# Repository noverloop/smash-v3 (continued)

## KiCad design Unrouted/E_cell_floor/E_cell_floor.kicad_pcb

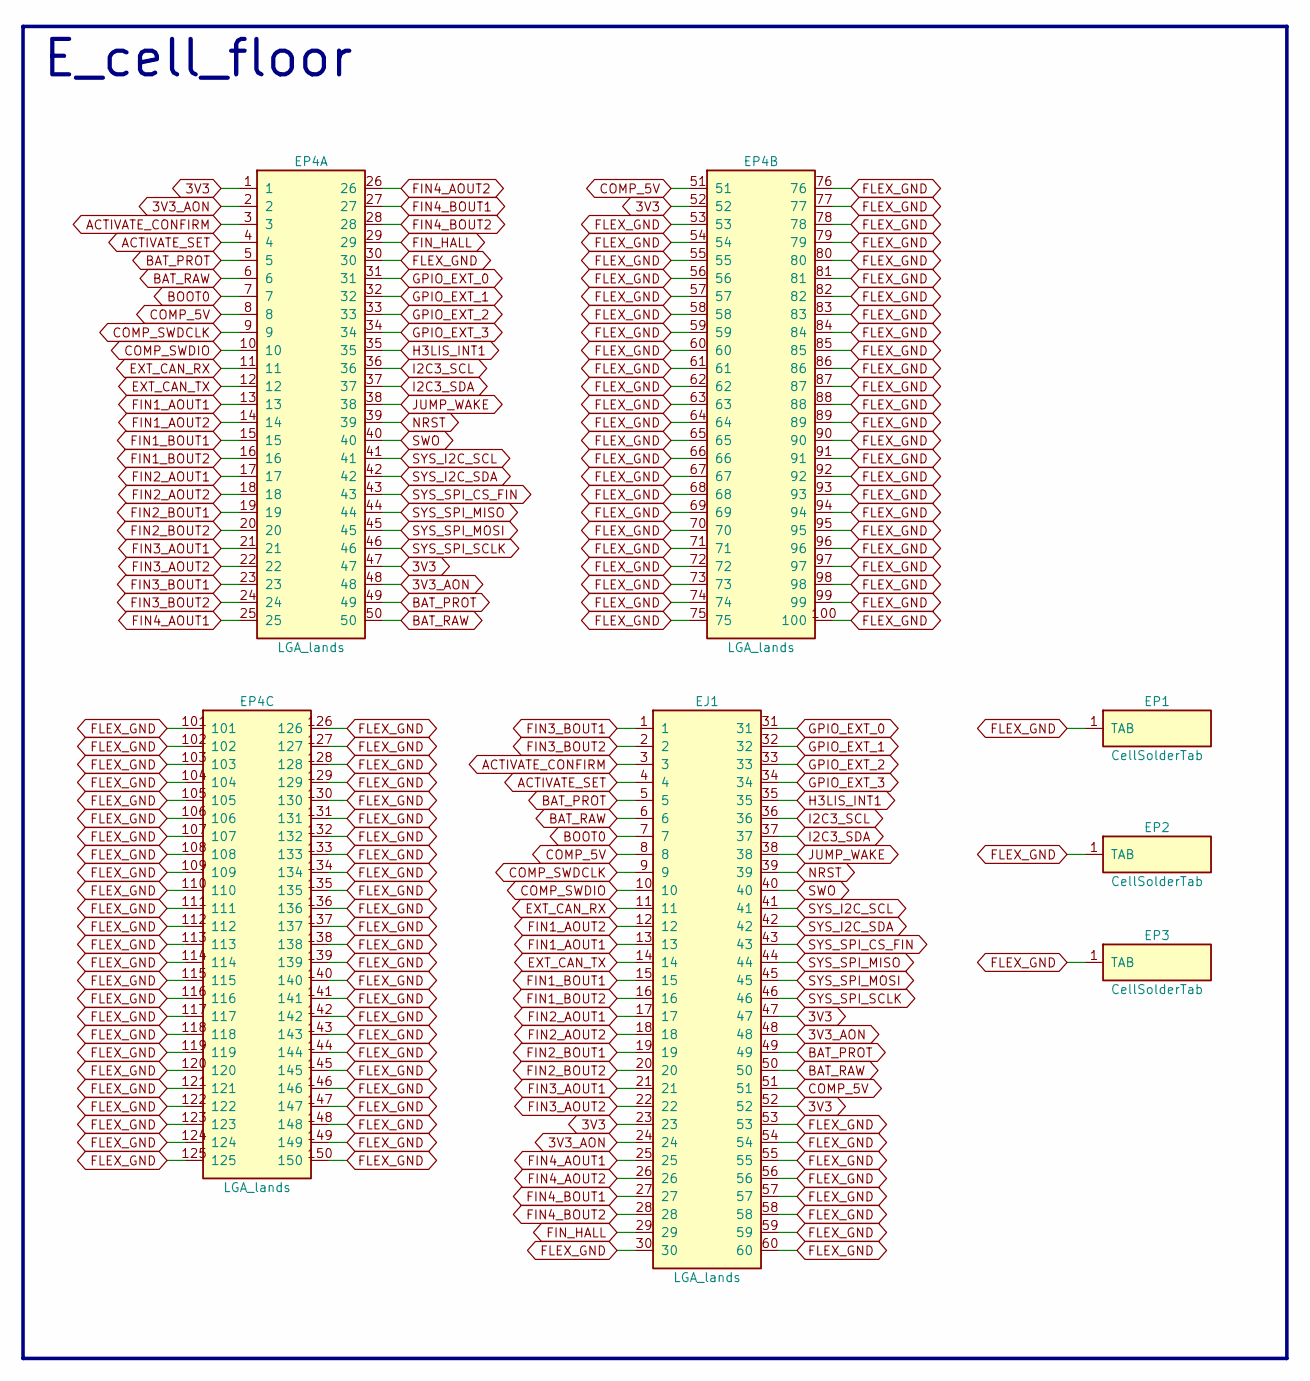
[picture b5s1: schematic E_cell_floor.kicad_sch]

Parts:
EJ1: LGA_lands; J_cell_floor_board_spacer_battery_1; MPN LGA_lands
EP1, EP2, EP3: CellSolderTab; CellSolderTab_placeholder; MPN CellSolderTab
EP4: LGA_lands; P_cell_floor_board_spacer_activation_interface_cell_floor_b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; MPN LGA_lands

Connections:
3V3: EJ1.23, EJ1.47, EJ1.52, EP4.1, EP4.47, EP4.52
3V3_AON: EJ1.24, EJ1.48, EP4.2, EP4.48
ACTIVATE_CONFIRM: EJ1.3, EP4.3
ACTIVATE_SET: EJ1.4, EP4.4
BAT_PROT: EJ1.5, EJ1.49, EP4.5, EP4.49
BAT_RAW: EJ1.6, EJ1.50, EP4.6, EP4.50
BOOT0: EJ1.7, EP4.7
COMP_5V: EJ1.8, EJ1.51, EP4.8, EP4.51
COMP_SWDCLK: EJ1.9, EP4.9
COMP_SWDIO: EJ1.10, EP4.10
EXT_CAN_RX: EJ1.11, EP4.11
EXT_CAN_TX: EJ1.14, EP4.12
FIN1_AOUT1: EJ1.13, EP4.13
FIN1_AOUT2: EJ1.12, EP4.14
FIN1_BOUT1: EJ1.15, EP4.15
FIN1_BOUT2: EJ1.16, EP4.16
FIN2_AOUT1: EJ1.17, EP4.17
FIN2_AOUT2: EJ1.18, EP4.18
FIN2_BOUT1: EJ1.19, EP4.19
FIN2_BOUT2: EJ1.20, EP4.20
FIN3_AOUT1: EJ1.21, EP4.21
FIN3_AOUT2: EJ1.22, EP4.22
FIN3_BOUT1: EJ1.1, EP4.23
FIN3_BOUT2: EJ1.2, EP4.24
FIN4_AOUT1: EJ1.25, EP4.25
FIN4_AOUT2: EJ1.26, EP4.26
FIN4_BOUT1: EJ1.27, EP4.27
FIN4_BOUT2: EJ1.28, EP4.28
FIN_HALL: EJ1.29, EP4.29
FLEX_GND: EJ1.30, EJ1.53, EJ1.54, EJ1.55, EJ1.56, EJ1.57, EJ1.58, EJ1.59, EJ1.60, EP1.1, EP2.1, EP3.1, EP4.30, EP4.53, EP4.54, EP4.55, EP4.56, EP4.57, EP4.58, EP4.59, EP4.60, EP4.61, EP4.62, EP4.63, EP4.64, EP4.65, EP4.66, EP4.67, EP4.68, EP4.69, EP4.70, EP4.71, EP4.72, EP4.73, EP4.74, EP4.75, EP4.76, EP4.77, EP4.78, EP4.79, EP4.80, EP4.81, EP4.82, EP4.83, EP4.84, EP4.85, EP4.86, EP4.87, EP4.88, EP4.89, EP4.90, EP4.91, EP4.92, EP4.93, EP4.94, EP4.95, EP4.96, EP4.97, EP4.98, EP4.99, EP4.100, EP4.101, EP4.102, EP4.103, EP4.104, EP4.105, EP4.106, EP4.107, EP4.108, EP4.109, EP4.110, EP4.111, EP4.112, EP4.113, EP4.114, EP4.115, EP4.116, EP4.117, EP4.118, EP4.119, EP4.120, EP4.121, EP4.122, EP4.123, EP4.124, EP4.125, EP4.126, EP4.127, EP4.128, EP4.129, EP4.130, EP4.131, EP4.132, EP4.133, EP4.134, EP4.135, EP4.136, EP4.137, EP4.138, EP4.139, EP4.140, EP4.141, EP4.142, EP4.143, EP4.144, EP4.145, EP4.146, EP4.147, EP4.148, EP4.149, EP4.150
GPIO_EXT_0: EJ1.31, EP4.31
GPIO_EXT_1: EJ1.32, EP4.32
GPIO_EXT_2: EJ1.33, EP4.33
GPIO_EXT_3: EJ1.34, EP4.34
H3LIS_INT1: EJ1.35, EP4.35
I2C3_SCL: EJ1.36, EP4.36
I2C3_SDA: EJ1.37, EP4.37
JUMP_WAKE: EJ1.38, EP4.38
NRST: EJ1.39, EP4.39
SWO: EJ1.40, EP4.40
SYS_I2C_SCL: EJ1.41, EP4.41
SYS_I2C_SDA: EJ1.42, EP4.42
SYS_SPI_CS_FIN: EJ1.43, EP4.43
SYS_SPI_MISO: EJ1.44, EP4.44
SYS_SPI_MOSI: EJ1.45, EP4.45
SYS_SPI_SCLK: EJ1.46, EP4.46

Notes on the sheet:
E_cell_floor

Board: 6 copper layers, 7 parts (1 on the bottom side), 46 nets, no tracks yet.

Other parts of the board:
EMH1, EMH2: smash_mech_potting

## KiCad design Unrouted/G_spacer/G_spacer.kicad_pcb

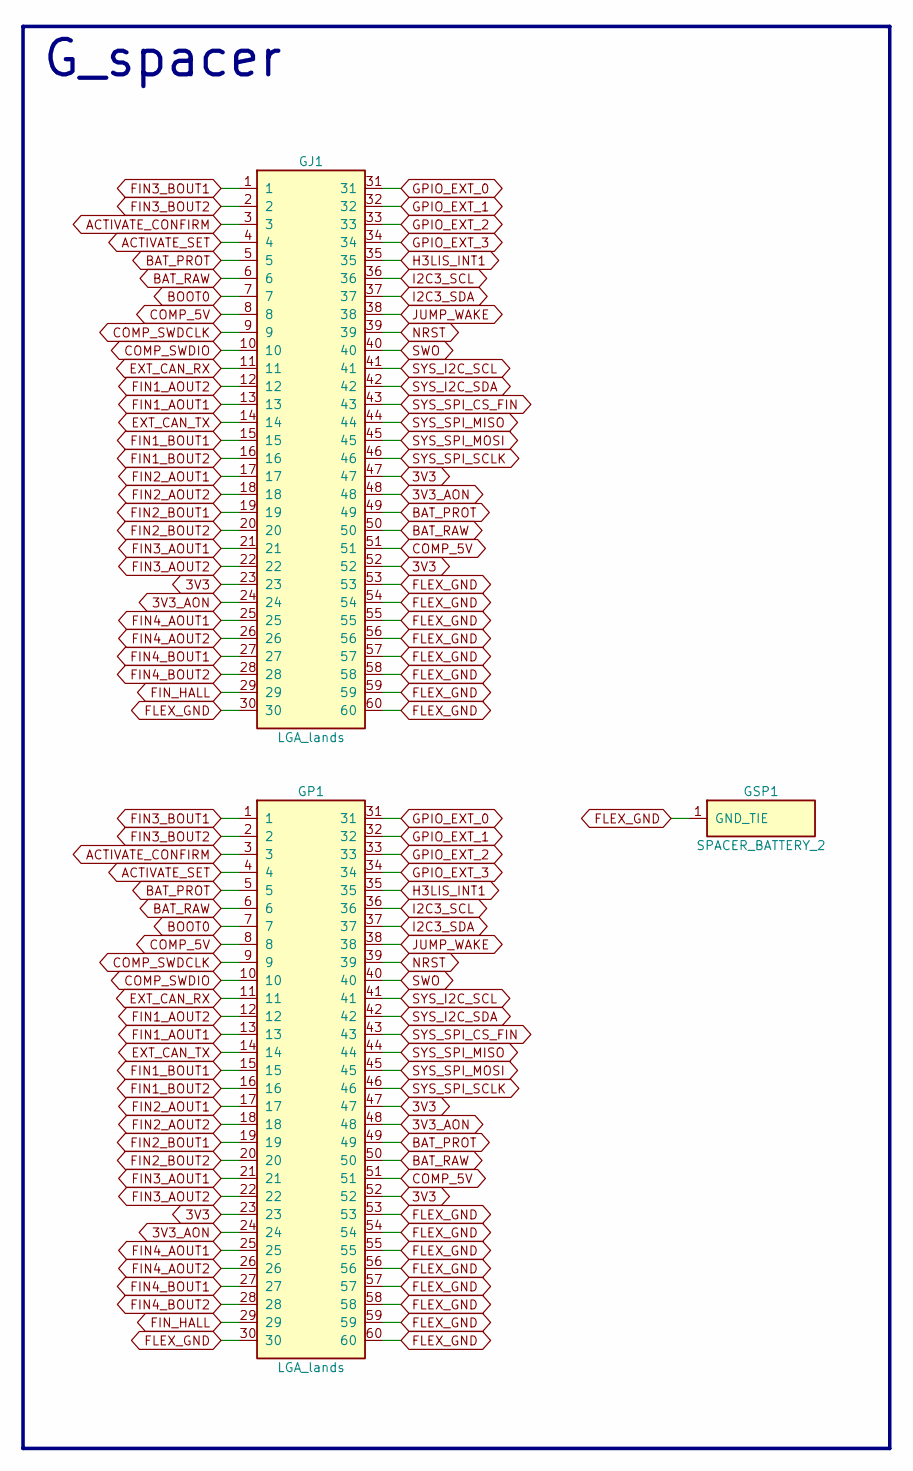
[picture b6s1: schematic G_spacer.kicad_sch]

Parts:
GJ1: LGA_lands; J_spacer_battery_2_top; MPN LGA_lands
GP1: LGA_lands; P_spacer_battery_2_bot; MPN LGA_lands
GSP1: SPACER_BATTERY_2; Spacer_Mechanical_34mm

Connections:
3V3: GJ1.23, GJ1.47, GJ1.52, GP1.23, GP1.47, GP1.52
3V3_AON: GJ1.24, GJ1.48, GP1.24, GP1.48
ACTIVATE_CONFIRM: GJ1.3, GP1.3
ACTIVATE_SET: GJ1.4, GP1.4
BAT_PROT: GJ1.5, GJ1.49, GP1.5, GP1.49
BAT_RAW: GJ1.6, GJ1.50, GP1.6, GP1.50
BOOT0: GJ1.7, GP1.7
COMP_5V: GJ1.8, GJ1.51, GP1.8, GP1.51
COMP_SWDCLK: GJ1.9, GP1.9
COMP_SWDIO: GJ1.10, GP1.10
EXT_CAN_RX: GJ1.11, GP1.11
EXT_CAN_TX: GJ1.14, GP1.14
FIN1_AOUT1: GJ1.13, GP1.13
FIN1_AOUT2: GJ1.12, GP1.12
FIN1_BOUT1: GJ1.15, GP1.15
FIN1_BOUT2: GJ1.16, GP1.16
FIN2_AOUT1: GJ1.17, GP1.17
FIN2_AOUT2: GJ1.18, GP1.18
FIN2_BOUT1: GJ1.19, GP1.19
FIN2_BOUT2: GJ1.20, GP1.20
FIN3_AOUT1: GJ1.21, GP1.21
FIN3_AOUT2: GJ1.22, GP1.22
FIN3_BOUT1: GJ1.1, GP1.1
FIN3_BOUT2: GJ1.2, GP1.2
FIN4_AOUT1: GJ1.25, GP1.25
FIN4_AOUT2: GJ1.26, GP1.26
FIN4_BOUT1: GJ1.27, GP1.27
FIN4_BOUT2: GJ1.28, GP1.28
FIN_HALL: GJ1.29, GP1.29
FLEX_GND: GJ1.30, GJ1.53, GJ1.54, GJ1.55, GJ1.56, GJ1.57, GJ1.58, GJ1.59, GJ1.60, GP1.30, GP1.53, GP1.54, GP1.55, GP1.56, GP1.57, GP1.58, GP1.59, GP1.60, GSP1.1
GPIO_EXT_0: GJ1.31, GP1.31
GPIO_EXT_1: GJ1.32, GP1.32
GPIO_EXT_2: GJ1.33, GP1.33
GPIO_EXT_3: GJ1.34, GP1.34
H3LIS_INT1: GJ1.35, GP1.35
I2C3_SCL: GJ1.36, GP1.36
I2C3_SDA: GJ1.37, GP1.37
JUMP_WAKE: GJ1.38, GP1.38
NRST: GJ1.39, GP1.39
SWO: GJ1.40, GP1.40
SYS_I2C_SCL: GJ1.41, GP1.41
SYS_I2C_SDA: GJ1.42, GP1.42
SYS_SPI_CS_FIN: GJ1.43, GP1.43
SYS_SPI_MISO: GJ1.44, GP1.44
SYS_SPI_MOSI: GJ1.45, GP1.45
SYS_SPI_SCLK: GJ1.46, GP1.46

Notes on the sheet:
G_spacer

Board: 2 copper layers, 4 parts (1 on the bottom side), 46 nets, no tracks yet.

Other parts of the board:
GMH1: smash_mech_potting

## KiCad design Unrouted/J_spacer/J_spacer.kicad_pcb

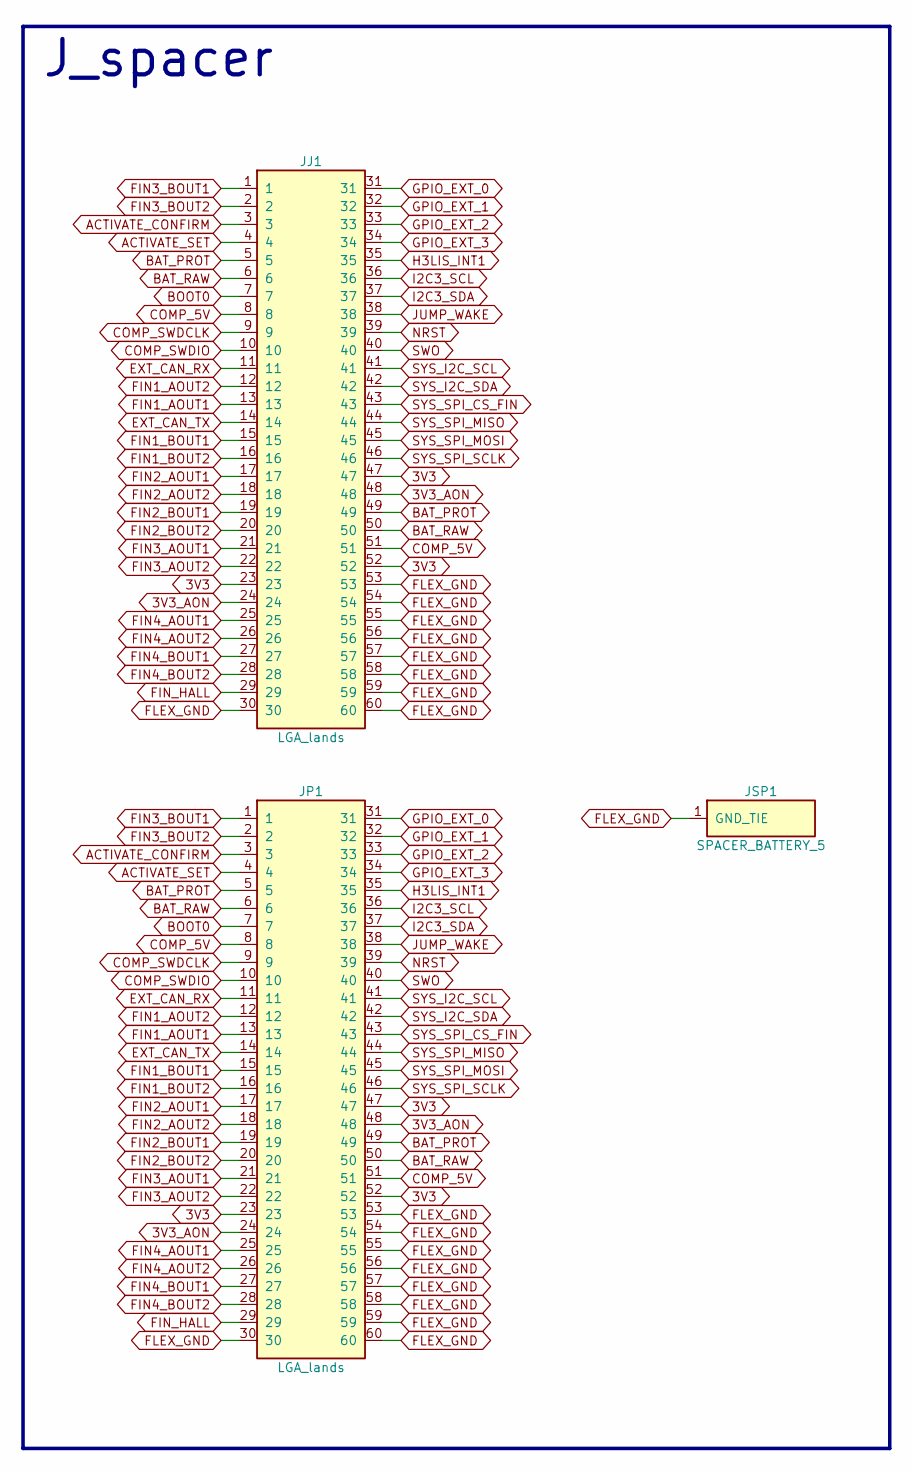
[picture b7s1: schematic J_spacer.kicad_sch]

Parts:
JJ1: LGA_lands; J_spacer_battery_5_top; MPN LGA_lands
JP1: LGA_lands; P_spacer_battery_5_bot; MPN LGA_lands
JSP1: SPACER_BATTERY_5; Spacer_Mechanical_34mm

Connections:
3V3: JJ1.23, JJ1.47, JJ1.52, JP1.23, JP1.47, JP1.52
3V3_AON: JJ1.24, JJ1.48, JP1.24, JP1.48
ACTIVATE_CONFIRM: JJ1.3, JP1.3
ACTIVATE_SET: JJ1.4, JP1.4
BAT_PROT: JJ1.5, JJ1.49, JP1.5, JP1.49
BAT_RAW: JJ1.6, JJ1.50, JP1.6, JP1.50
BOOT0: JJ1.7, JP1.7
COMP_5V: JJ1.8, JJ1.51, JP1.8, JP1.51
COMP_SWDCLK: JJ1.9, JP1.9
COMP_SWDIO: JJ1.10, JP1.10
EXT_CAN_RX: JJ1.11, JP1.11
EXT_CAN_TX: JJ1.14, JP1.14
FIN1_AOUT1: JJ1.13, JP1.13
FIN1_AOUT2: JJ1.12, JP1.12
FIN1_BOUT1: JJ1.15, JP1.15
FIN1_BOUT2: JJ1.16, JP1.16
FIN2_AOUT1: JJ1.17, JP1.17
FIN2_AOUT2: JJ1.18, JP1.18
FIN2_BOUT1: JJ1.19, JP1.19
FIN2_BOUT2: JJ1.20, JP1.20
FIN3_AOUT1: JJ1.21, JP1.21
FIN3_AOUT2: JJ1.22, JP1.22
FIN3_BOUT1: JJ1.1, JP1.1
FIN3_BOUT2: JJ1.2, JP1.2
FIN4_AOUT1: JJ1.25, JP1.25
FIN4_AOUT2: JJ1.26, JP1.26
FIN4_BOUT1: JJ1.27, JP1.27
FIN4_BOUT2: JJ1.28, JP1.28
FIN_HALL: JJ1.29, JP1.29
FLEX_GND: JJ1.30, JJ1.53, JJ1.54, JJ1.55, JJ1.56, JJ1.57, JJ1.58, JJ1.59, JJ1.60, JP1.30, JP1.53, JP1.54, JP1.55, JP1.56, JP1.57, JP1.58, JP1.59, JP1.60, JSP1.1
GPIO_EXT_0: JJ1.31, JP1.31
GPIO_EXT_1: JJ1.32, JP1.32
GPIO_EXT_2: JJ1.33, JP1.33
GPIO_EXT_3: JJ1.34, JP1.34
H3LIS_INT1: JJ1.35, JP1.35
I2C3_SCL: JJ1.36, JP1.36
I2C3_SDA: JJ1.37, JP1.37
JUMP_WAKE: JJ1.38, JP1.38
NRST: JJ1.39, JP1.39
SWO: JJ1.40, JP1.40
SYS_I2C_SCL: JJ1.41, JP1.41
SYS_I2C_SDA: JJ1.42, JP1.42
SYS_SPI_CS_FIN: JJ1.43, JP1.43
SYS_SPI_MISO: JJ1.44, JP1.44
SYS_SPI_MOSI: JJ1.45, JP1.45
SYS_SPI_SCLK: JJ1.46, JP1.46

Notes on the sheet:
J_spacer

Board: 2 copper layers, 4 parts (1 on the bottom side), 46 nets, no tracks yet.

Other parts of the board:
JMH1: smash_mech_potting
